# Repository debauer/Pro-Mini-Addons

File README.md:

# Pro-Mini-Addons
Some Addon Boards for the Arduino Pro Mini

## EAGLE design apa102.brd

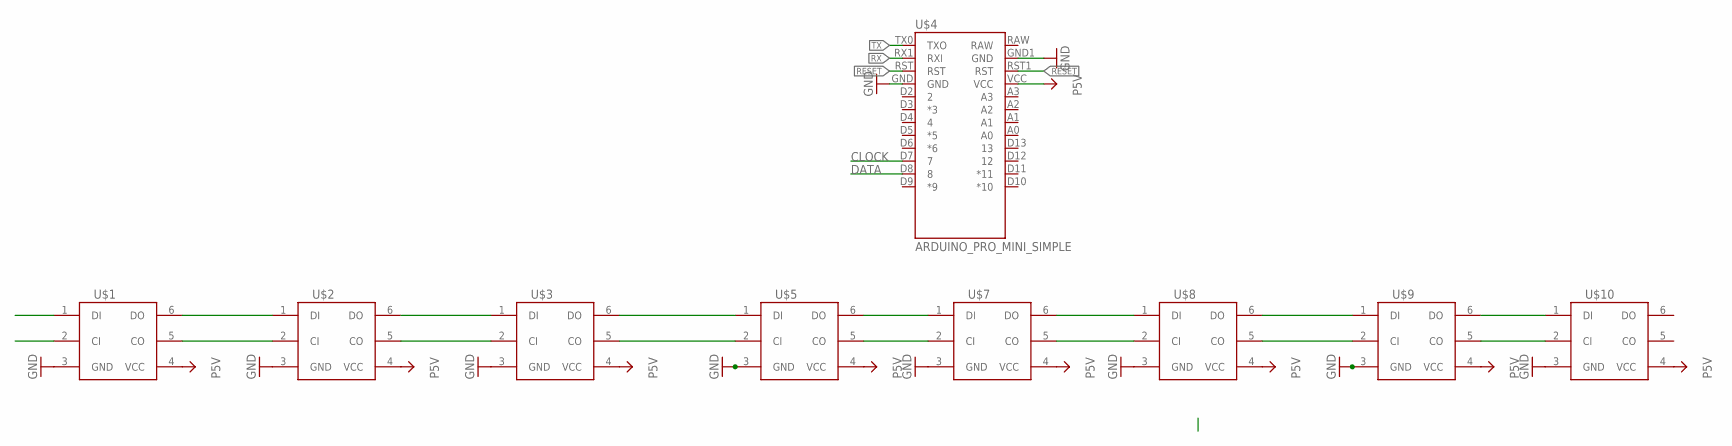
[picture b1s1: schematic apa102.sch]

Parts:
U$1, U$2, U$3, U$5, U$7, U$8, U$9, U$10: APA102; LED5050
U$4: ARDUINO_PRO_MINI_SIMPLE; PRO_MINI_SIMPLE

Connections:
CLOCK: U$1.2 (CI), U$4.D7 (7)
DATA: U$1.1 (DI), U$4.D8 (8)
GND: U$1.3 (GND), U$2.3 (GND), U$3.3 (GND), U$4.GND, U$4.GND1 (GND), U$5.3 (GND), U$7.3 (GND), U$8.3 (GND), U$9.3 (GND), U$10.3 (GND)
unnamed: U$1.6 (DO), U$2.1 (DI)
unnamed: U$1.5 (CO), U$2.2 (CI)
unnamed: U$3.6 (DO), U$5.1 (DI)
unnamed: U$2.6 (DO), U$3.1 (DI)
unnamed: U$2.5 (CO), U$3.2 (CI)
unnamed: U$3.5 (CO), U$5.2 (CI)
unnamed: U$5.6 (DO), U$7.1 (DI)
unnamed: U$5.5 (CO), U$7.2 (CI)
unnamed: U$8.6 (DO), U$9.1 (DI)
unnamed: U$7.6 (DO), U$8.1 (DI)
unnamed: U$7.5 (CO), U$8.2 (CI)
unnamed: U$8.5 (CO), U$9.2 (CI)
unnamed: U$9.6 (DO), U$10.1 (DI)
unnamed: U$9.5 (CO), U$10.2 (CI)
P5V: U$1.4 (VCC), U$2.4 (VCC), U$3.4 (VCC), U$4.VCC, U$5.4 (VCC), U$7.4 (VCC), U$8.4 (VCC), U$9.4 (VCC), U$10.4 (VCC)
RESET: U$4.RST, U$4.RST1 (RST)
RX: U$4.RX1 (RXI)
TX: U$4.TX0 (TXO)

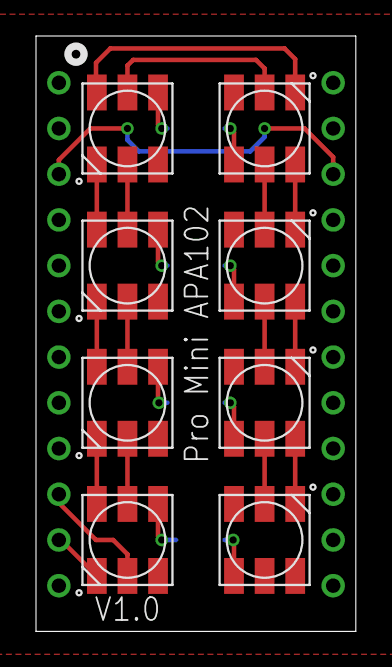
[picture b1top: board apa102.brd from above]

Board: 2 copper layers, 17.8 x 33.1 mm, 10 parts (1 on the bottom side), 19 nets.

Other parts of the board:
U$12: KALT!ELEKTRONIK

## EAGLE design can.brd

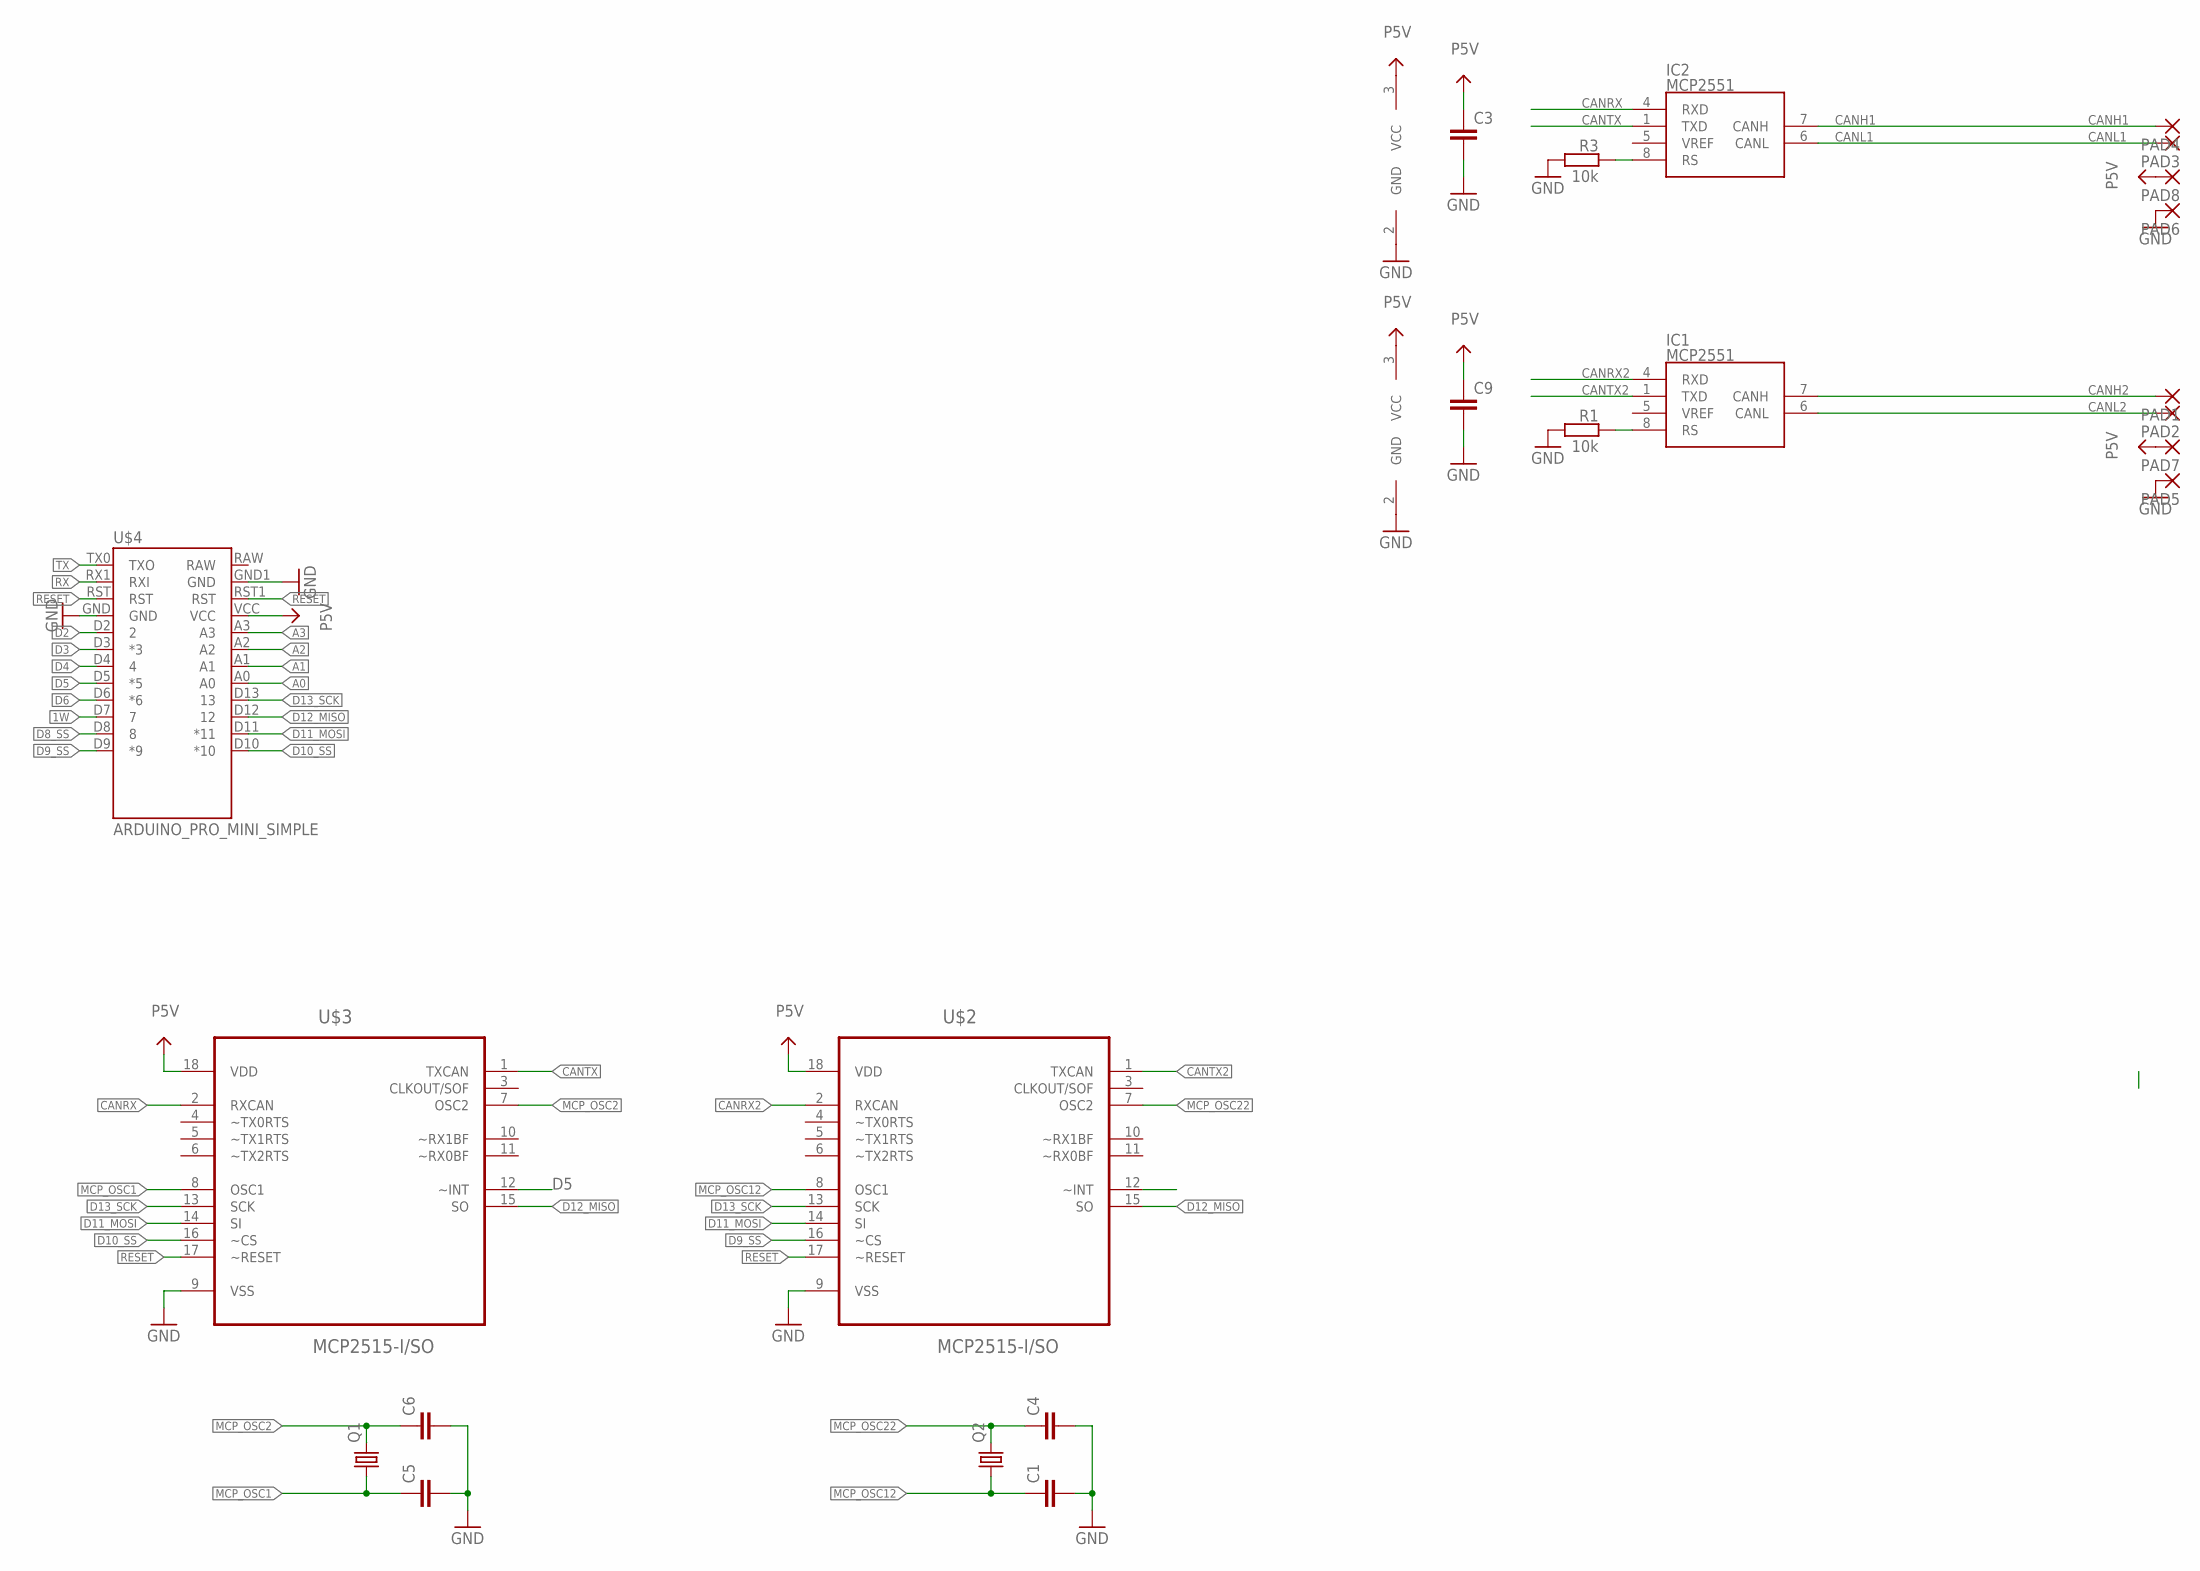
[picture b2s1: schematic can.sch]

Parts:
C1, C3, C4, C5, C6, C9: C-EUC0805; C0805
IC1, IC2: MCP2551; SO-8
PAD1, PAD2, PAD3, PAD4, PAD5, PAD6, PAD7, PAD8: SMD2; SMD1,27-2,54
Q1, Q2: CRYSTALHC49S; HC49/S
R1, R3: 10k; R0603
U$2, U$3: MCP2515-I/SO; SOIC127P1034X264-18N
U$4: ARDUINO_PRO_MINI_SIMPLE; PRO_MINI_SIMPLE

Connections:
1W: U$4.D7 (7)
A0: U$4.A0
A1: U$4.A1
A2: U$4.A2
A3: U$4.A3
CANH1: IC2.7 (CANH), PAD4.1
CANH2: IC1.7 (CANH), PAD1.1
CANL1: IC2.6 (CANL), PAD3.1
CANL2: IC1.6 (CANL), PAD2.1
CANRX: IC2.4 (RXD), U$3.2 (RXCAN)
CANRX2: IC1.4 (RXD), U$2.2 (RXCAN)
CANTX: IC2.1 (TXD), U$3.1 (TXCAN)
CANTX2: IC1.1 (TXD), U$2.1 (TXCAN)
D2: U$4.D2 (2)
D3: U$4.D3 (*3)
D4: U$4.D4 (4)
D5: U$3.12 (~INT), U$4.D5 (*5)
D6: U$2.12 (~INT), U$4.D6 (*6)
D8_SS: U$4.D8 (8)
D9_SS: U$2.16 (~CS), U$4.D9 (*9)
D10_SS: U$3.16 (~CS), U$4.D10 (*10)
D11_MOSI: U$2.14 (SI), U$3.14 (SI), U$4.D11 (*11)
D12_MISO: U$2.15 (SO), U$3.15 (SO), U$4.D12 (12)
D13_SCK: U$2.13 (SCK), U$3.13 (SCK), U$4.D13 (13)
GND: C1.2, C3.2, C4.2, C5.2, C6.2, C9.2, IC1.2 (GND), IC2.2 (GND), PAD5.1, PAD6.1, R1.2, R3.2, U$2.9 (VSS), U$3.9 (VSS), U$4.GND, U$4.GND1 (GND)
MCP_OSC1: C5.1, Q1.1, U$3.8 (OSC1)
MCP_OSC2: C6.1, Q1.2, U$3.7 (OSC2)
MCP_OSC12: C1.1, Q2.1, U$2.8 (OSC1)
MCP_OSC22: C4.1, Q2.2, U$2.7 (OSC2)
unnamed: IC1.8 (RS), R1.1
unnamed: IC2.8 (RS), R3.1
P5V: C3.1, C9.1, IC1.3 (VCC), IC2.3 (VCC), PAD7.1, PAD8.1, U$2.18 (VDD), U$3.18 (VDD), U$4.VCC
RESET: U$2.17 (~RESET), U$3.17 (~RESET), U$4.RST, U$4.RST1 (RST)
RX: U$4.RX1 (RXI)
TX: U$4.TX0 (TXO)

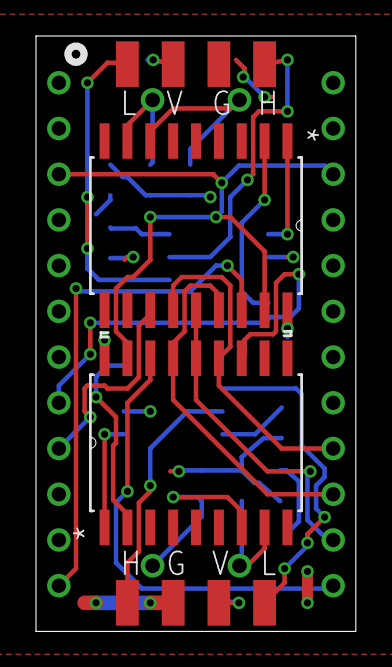
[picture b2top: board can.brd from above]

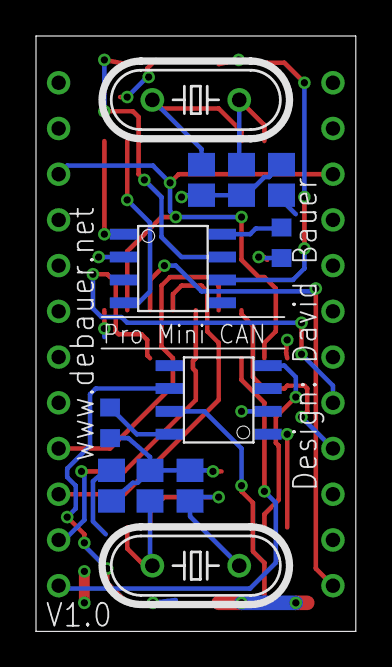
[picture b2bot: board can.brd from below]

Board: 2 copper layers, 17.8 x 33.1 mm, 23 parts (12 on the bottom side), 24 nets.

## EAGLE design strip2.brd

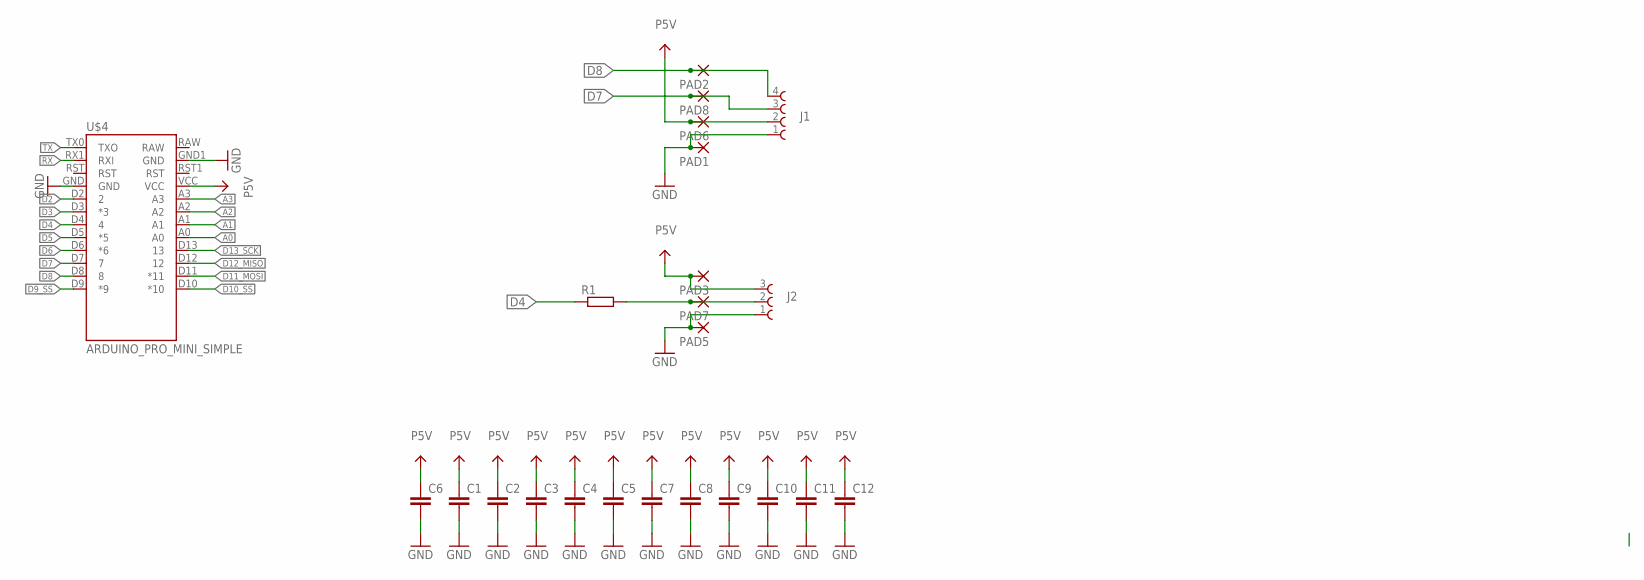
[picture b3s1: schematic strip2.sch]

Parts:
C1, C2, C3, C4, C5, C6: C-EUC1210K; C1210K
C7, C8, C9, C10, C11, C12: C-EUC1206K; C1206K
J1: 691322110004
J2: 691322110003
PAD1, PAD2, PAD3, PAD5, PAD6, PAD7, PAD8: SMD2; SMD1,27-2,54
R1: R-EU_R0805; R0805
U$4: ARDUINO_PRO_MINI_SIMPLE; PRO_MINI_SIMPLE

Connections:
A0: U$4.A0
A1: U$4.A1
A2: U$4.A2
A3: U$4.A3
D2: U$4.D2 (2)
D3: U$4.D3 (*3)
D4: R1.1, U$4.D4 (4)
D5: U$4.D5 (*5)
D6: U$4.D6 (*6)
D7: J1.3 (2), PAD8.1, U$4.D7 (7)
D8: J1.4 (1), PAD2.1, U$4.D8 (8)
D9_SS: U$4.D9 (*9)
D10_SS: U$4.D10 (*10)
D11_MOSI: U$4.D11 (*11)
D12_MISO: U$4.D12 (12)
D13_SCK: U$4.D13 (13)
GND: C1.2, C2.2, C3.2, C4.2, C5.2, C6.2, C7.2, C8.2, C9.2, C10.2, C11.2, C12.2, J1.1 (4), J2.1 (3), PAD1.1, PAD5.1, U$4.GND, U$4.GND1 (GND)
unnamed: J2.2, PAD7.1, R1.2
P5V: C1.1, C2.1, C3.1, C4.1, C5.1, C6.1, C7.1, C8.1, C9.1, C10.1, C11.1, C12.1, J1.2 (3), J2.3 (1), PAD3.1, PAD6.1, U$4.VCC
RX: U$4.RX1 (RXI)
TX: U$4.TX0 (TXO)

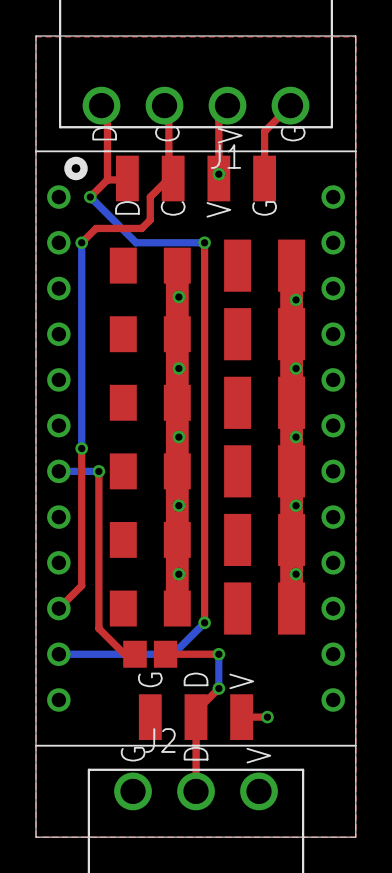
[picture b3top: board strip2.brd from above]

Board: 2 copper layers, 17.8 x 44.5 mm, 24 parts (1 on the bottom side), 6 nets.

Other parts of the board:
U$1: KALT!ELEKTRONIK

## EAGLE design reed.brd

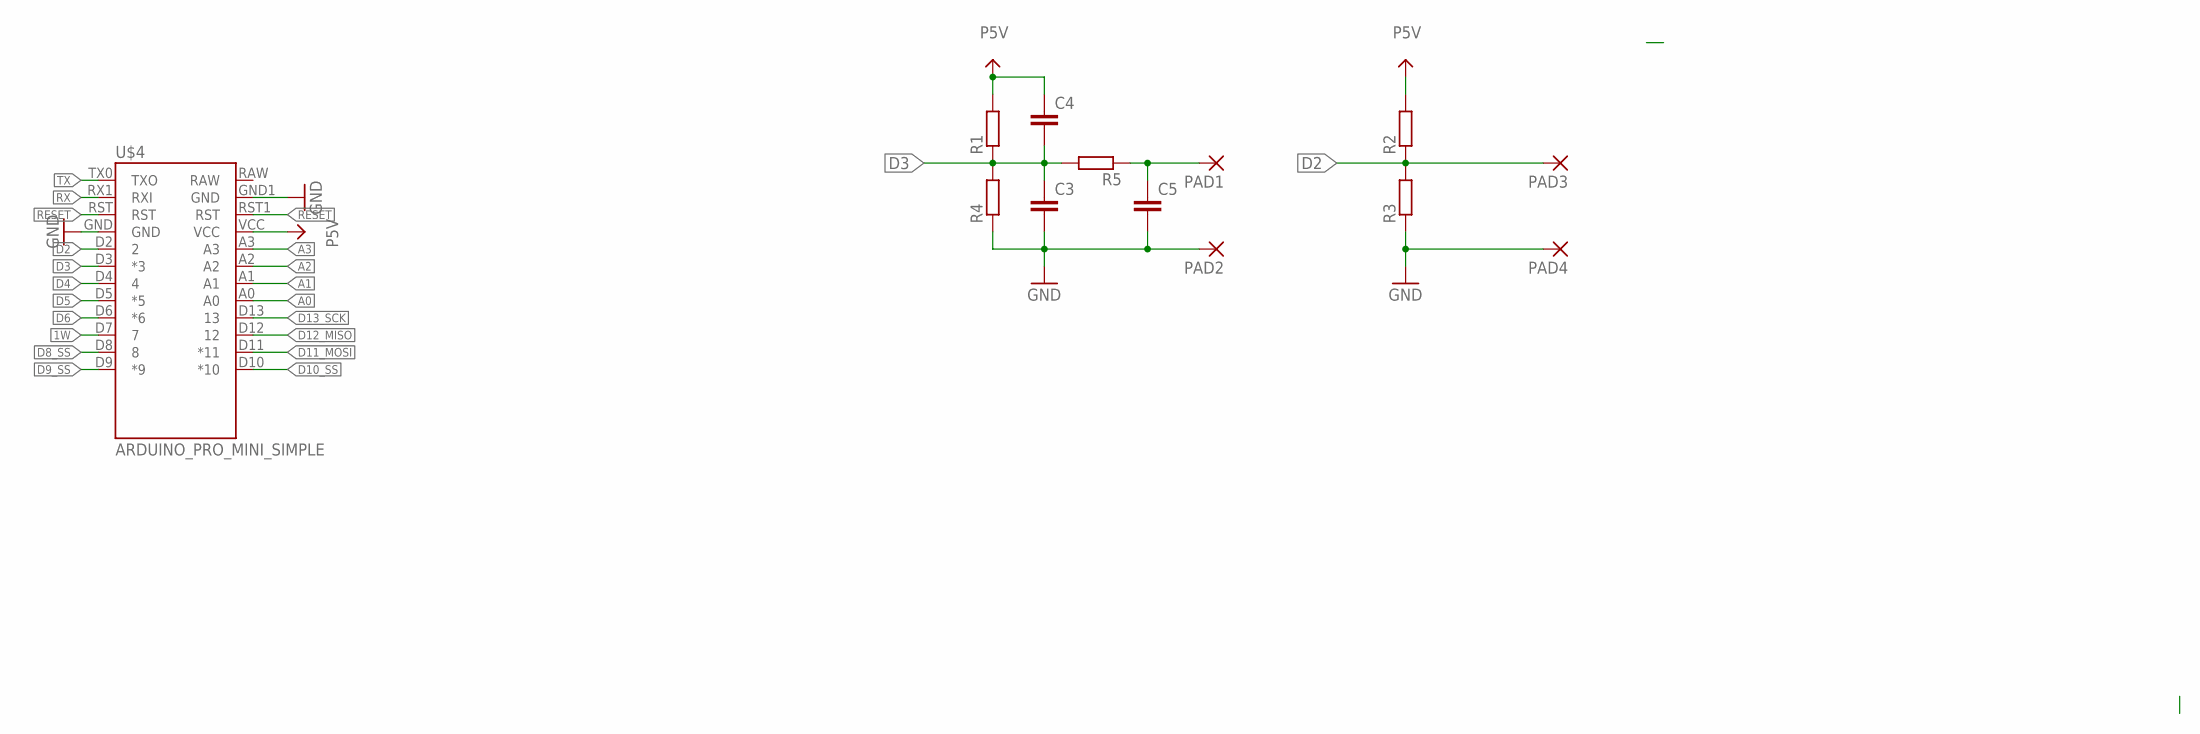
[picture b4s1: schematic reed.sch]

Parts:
C3, C4, C5: C-EUC0603K; C0603K
PAD1, PAD2, PAD3, PAD4: SMD2; SMD1,27-2,54
R1, R2, R3, R4, R5: R-EU_R0603; R0603
U$4: ARDUINO_PRO_MINI_SIMPLE; PRO_MINI_SIMPLE

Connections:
1W: U$4.D7 (7)
A0: U$4.A0
A1: U$4.A1
A2: U$4.A2
A3: U$4.A3
D2: PAD3.1, R2.1, R3.2, U$4.D2 (2)
D3: C3.1, C4.2, R1.1, R4.2, R5.2, U$4.D3 (*3)
D4: U$4.D4 (4)
D5: U$4.D5 (*5)
D6: U$4.D6 (*6)
D8_SS: U$4.D8 (8)
D9_SS: U$4.D9 (*9)
D10_SS: U$4.D10 (*10)
D11_MOSI: U$4.D11 (*11)
D12_MISO: U$4.D12 (12)
D13_SCK: U$4.D13 (13)
GND: C3.2, C5.2, PAD2.1, PAD4.1, R3.1, R4.1, U$4.GND, U$4.GND1 (GND)
unnamed: C5.1, PAD1.1, R5.1
P5V: C4.1, R1.2, R2.2, U$4.VCC
RESET: U$4.RST, U$4.RST1 (RST)
RX: U$4.RX1 (RXI)
TX: U$4.TX0 (TXO)

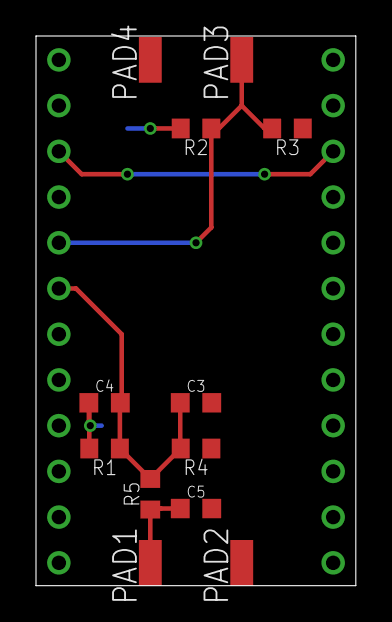
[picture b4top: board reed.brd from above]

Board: 2 copper layers, 17.8 x 30.5 mm, 13 parts (0 on the bottom side), 6 nets.

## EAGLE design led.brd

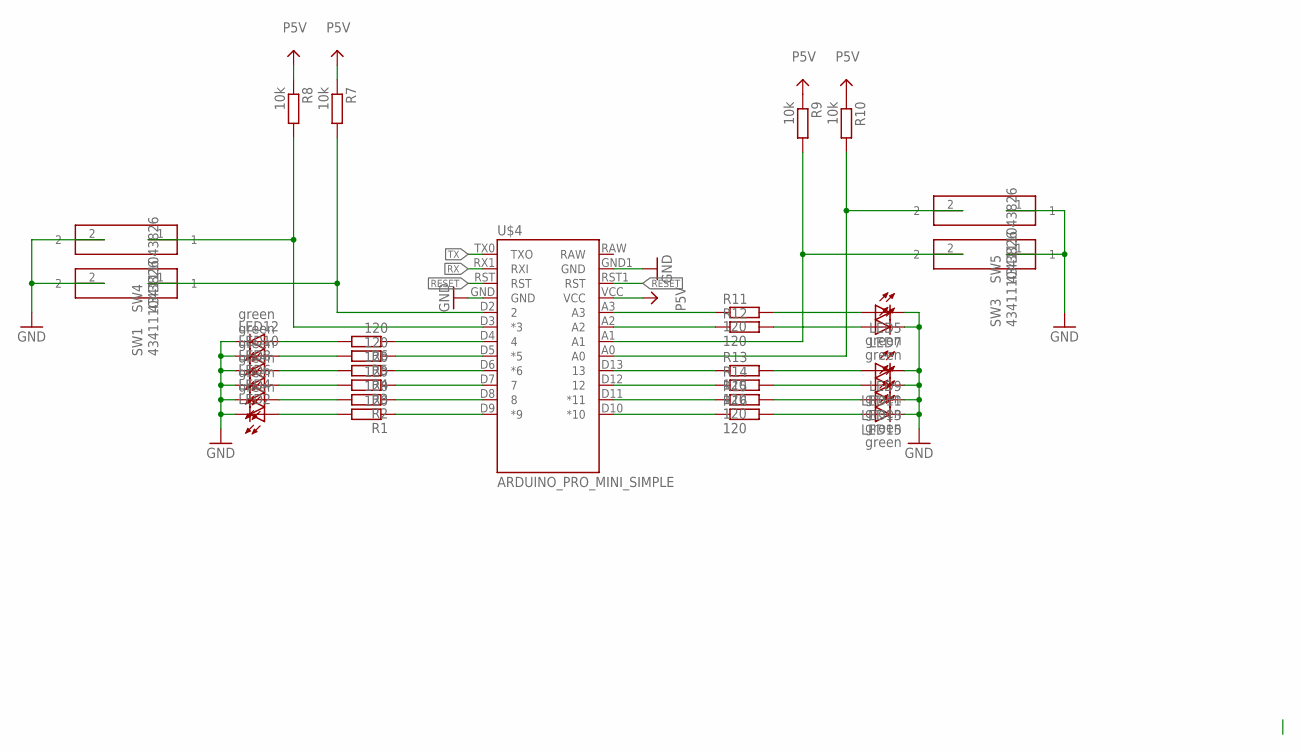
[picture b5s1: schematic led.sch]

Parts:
LED2, LED4, LED5, LED6, LED7, LED8, LED9, LED10, LED11, LED12, LED13, LED15: green; CHIPLED_0805
R1, R2, R3, R4, R5, R6, R11, R12, R13, R14, R15, R16: 120; R0805
R7, R8, R9, R10: 10k; R0805
SW1, SW3, SW4, SW5: 434111043826
U$4: ARDUINO_PRO_MINI_SIMPLE; PRO_MINI_SIMPLE

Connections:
GND: LED2.C, LED4.C, LED5.C, LED6.C, LED7.C, LED8.C, LED9.C, LED10.C, LED11.C, LED12.C, LED13.C, LED15.C, SW1.2, SW3.1, SW4.2, SW5.1, U$4.GND, U$4.GND1 (GND)
unnamed: R7.2, SW1.1, U$4.D2 (2)
unnamed: R8.2, SW4.1, U$4.D3 (*3)
unnamed: LED5.A, R11.2
unnamed: LED7.A, R12.2
unnamed: LED9.A, R13.2
unnamed: LED11.A, R14.2
unnamed: LED13.A, R15.2
unnamed: LED15.A, R16.2
unnamed: R11.1, U$4.A3
unnamed: R12.1, U$4.A2
unnamed: R9.2, SW3.2, U$4.A1
unnamed: R10.2, SW5.2, U$4.A0
unnamed: R13.1, U$4.D13 (13)
unnamed: R14.1, U$4.D12 (12)
unnamed: R15.1, U$4.D11 (*11)
unnamed: R16.1, U$4.D10 (*10)
unnamed: LED2.A, R1.2
unnamed: LED4.A, R2.2
unnamed: LED6.A, R3.2
unnamed: LED8.A, R4.2
unnamed: LED10.A, R5.2
unnamed: LED12.A, R6.2
unnamed: R1.1, U$4.D9 (*9)
unnamed: R2.1, U$4.D8 (8)
unnamed: R3.1, U$4.D7 (7)
unnamed: R4.1, U$4.D6 (*6)
unnamed: R5.1, U$4.D5 (*5)
unnamed: R6.1, U$4.D4 (4)
P5V: R7.1, R8.1, R9.1, R10.1, U$4.VCC
RESET: U$4.RST, U$4.RST1 (RST)
RX: U$4.RX1 (RXI)
TX: U$4.TX0 (TXO)

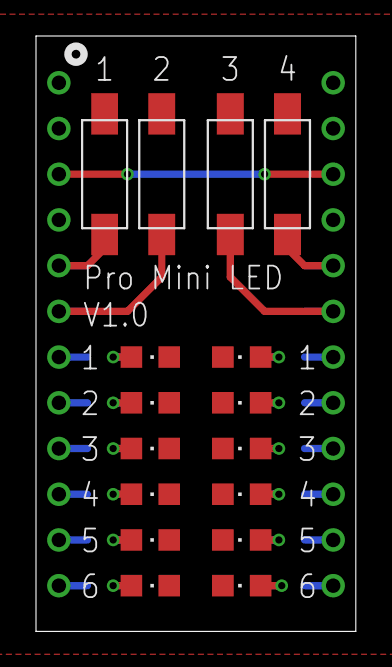
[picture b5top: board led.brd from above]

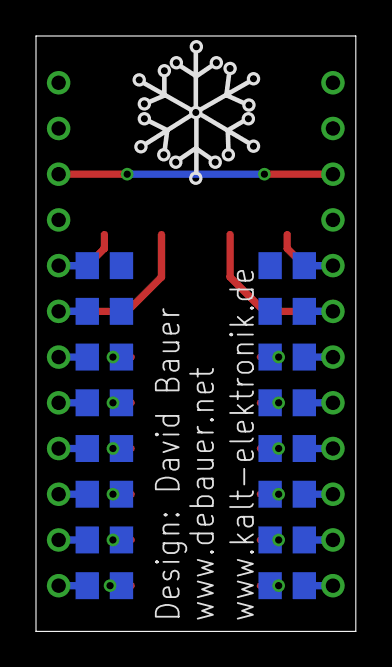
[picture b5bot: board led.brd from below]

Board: 2 copper layers, 17.8 x 33.1 mm, 34 parts (17 on the bottom side), 31 nets.

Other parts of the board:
U$1: SNOW

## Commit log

2019-01-29 added designs

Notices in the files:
parts and their libraries:
Wuerth_Elektronik_Switch: Copyright: Würth Elektronik
